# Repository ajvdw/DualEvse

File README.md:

# DualEvse
 Dual EVSE board (Arduino Nano Shield)

Supports charging of 2 vehicles by load balancing between them.
DualEVSE firmware is under development.

You can use OpenEVSE firmware with minor changes if you only need a single charge port.

Please note: The current hardware version (0.9) is not tested yet.

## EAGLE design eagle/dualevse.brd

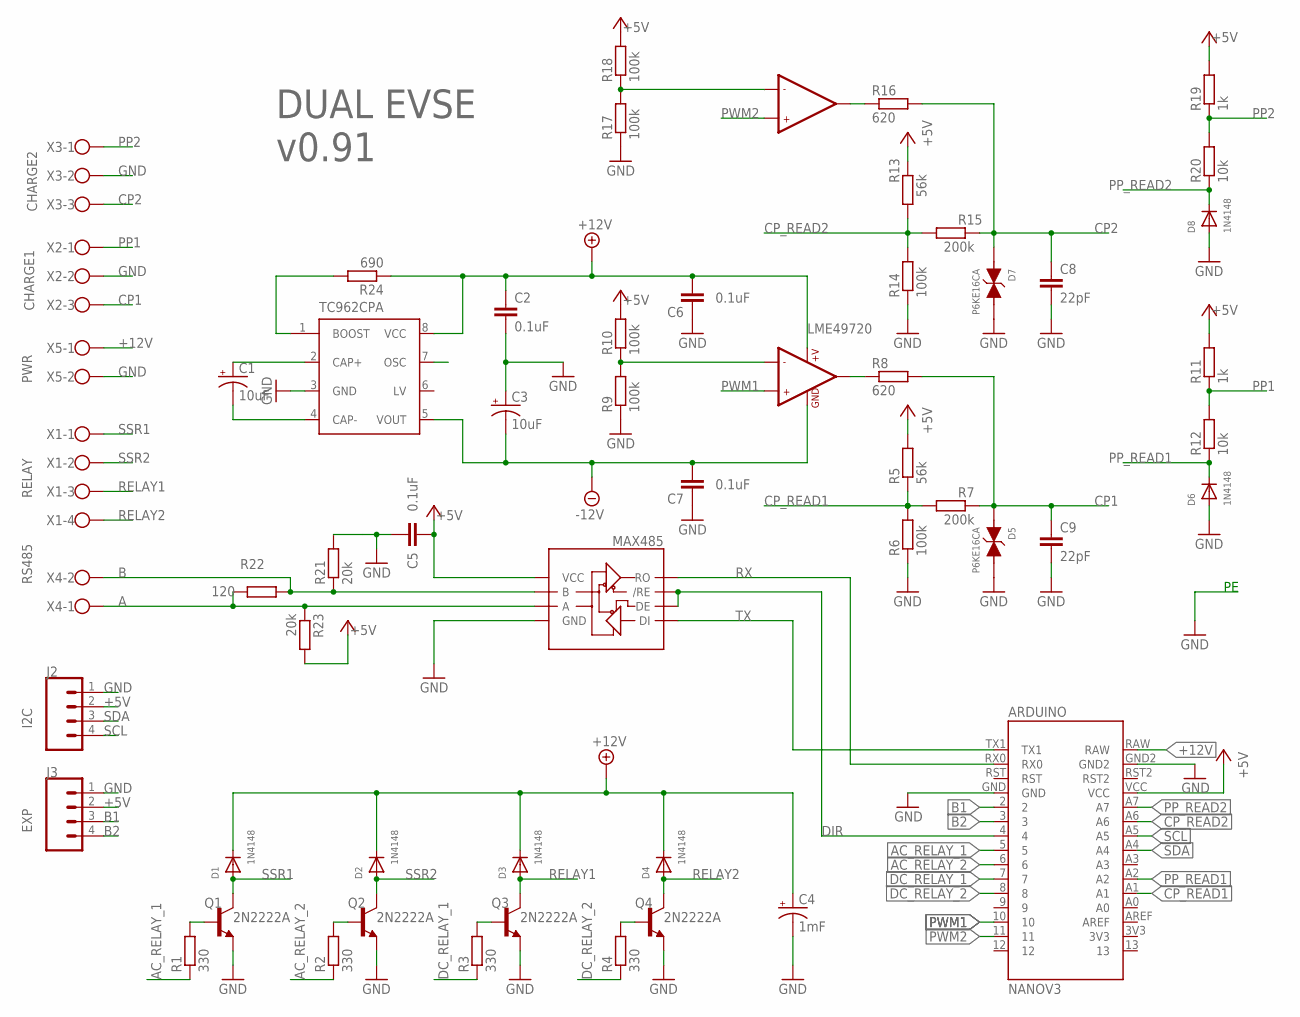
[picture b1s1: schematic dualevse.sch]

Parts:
ARDUINO: NANOV3
C1, C3: 10uF; CPOL-RADIAL-2.5MM-5MM
C2, C5, C6, C7: 0.1uF; CAP-PTH-SMALL-KIT
C4: 1mF; CPOL-RADIAL-5MM-10MM
C8, C9: 22pF; CAP-PTH-2.54
D1, D2, D3, D4, D6, D8: 1N4148; DO-1N4148
D5, D7: P6KE16CA; C4111-15
J2: I2C; MOLEX-1X4
J3: EXP; MOLEX-1X4
LME49720: LME49720; TEXAS_DIL08
MAX485: SPARKFUN-IC-COMMS_RS485; TEXAS_DIL08
Q1, Q2, Q3, Q4: 2N2222A; TO18
R1, R2, R3, R4: 330; 0207/10
R5, R13: 56k; 0207/10
R6, R9, R10, R14, R17, R18: 100k; 0207/10
R7, R15: 200k; 0207/10
R8, R16: 620; 0207/10
R11, R19: 1k; 0207/10
R12, R20: 10k; 0207/10
R21, R23: 20k; 0207/10
R22: 120; 0207/10
R24: 690; 0207/10
TC962CPA: TEXAS_TL7660; TEXAS_DIL08
X1: RELAY; W237-4
X2: CHARGE1; W237-103
X3: CHARGE2; W237-103
X4: RS485; W237-102
X5: PWR; W237-102

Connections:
+5V: ARDUINO.VCC, C5.2, J2.2, J3.2, MAX485.8 (VCC), R5.2, R10.2, R11.2, R13.2, R18.2, R19.2, R23.2
+12V: ARDUINO.RAW, C2.1, C4.+, C6.1, D1.C, D2.C, D3.C, D4.C, LME49720.8 (+V), R24.1, TC962CPA.8 (VCC), X5.1
-12V: C3.2 (-), C7.2, LME49720.4 (GND), TC962CPA.5 (VOUT)
A: MAX485.6 (A), R22.1, R23.1, X4.1
AC_RELAY_1: ARDUINO.5, R1.1
AC_RELAY_2: ARDUINO.6, R2.1
B: MAX485.7 (B), R21.1, R22.2, X4.2
B1: ARDUINO.2, J3.3
B2: ARDUINO.3, J3.4
CP1: C9.1, D5.A (1), R7.2, R8.2, X2.3
CP2: C8.1, D7.A (1), R15.2, R16.2, X3.3
CP_READ1: ARDUINO.A1, R5.1, R6.2, R7.1
CP_READ2: ARDUINO.A6, R13.1, R14.2, R15.1
DC_RELAY_1: ARDUINO.7, R3.1
DC_RELAY_2: ARDUINO.8, R4.1
DIR: ARDUINO.4, MAX485.2 (/RE), MAX485.3 (DE)
GND: ARDUINO.GND, ARDUINO.GND2, C2.2, C3.1 (+), C4.-, C5.1, C6.2, C7.1, C8.2, C9.2, D5.C (2), D6.A, D7.C (2), D8.A, J2.1, J3.1, MAX485.5 (GND), Q1.1 (E), Q2.1 (E), Q3.1 (E), Q4.1 (E), R6.1, R9.1, R14.1, R17.1, R21.2, TC962CPA.3 (GND), X2.2, X3.2, X5.2
unnamed: LME49720.6 (-IN2), R17.2, R18.1
unnamed: Q3.2 (B), R3.2
unnamed: Q4.2 (B), R4.2
unnamed: LME49720.7 (OUT2), R16.1
unnamed: Q1.2 (B), R1.2
unnamed: Q2.2 (B), R2.2
unnamed: R24.2, TC962CPA.1 (BOOST)
unnamed: LME49720.2 (-IN1), R9.2, R10.1
unnamed: LME49720.1 (OUT1), R8.1
unnamed: C1.1 (+), TC962CPA.2 (CAP+)
unnamed: C1.2 (-), TC962CPA.4 (CAP-)
NC: TC962CPA.7 (OSC)
PP1: R11.1, R12.2, X2.1
PP2: R19.1, R20.2, X3.1
PP_READ1: ARDUINO.A2, D6.C, R12.1
PP_READ2: ARDUINO.A7, D8.C, R20.1
PWM1: ARDUINO.10, LME49720.3 (+IN1)
PWM2: ARDUINO.11, LME49720.5 (+IN2)
RELAY1: D3.A, Q3.3 (C), X1.3
RELAY2: D4.A, Q4.3 (C), X1.4
RX: ARDUINO.RX0, MAX485.1 (RO)
SCL: ARDUINO.A5, J2.4
SDA: ARDUINO.A4, J2.3
SSR1: D1.A, Q1.3 (C), X1.1
SSR2: D2.A, Q2.3 (C), X1.2
TX: ARDUINO.TX1, MAX485.4 (DI)

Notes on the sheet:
DUAL EVSE v0.91

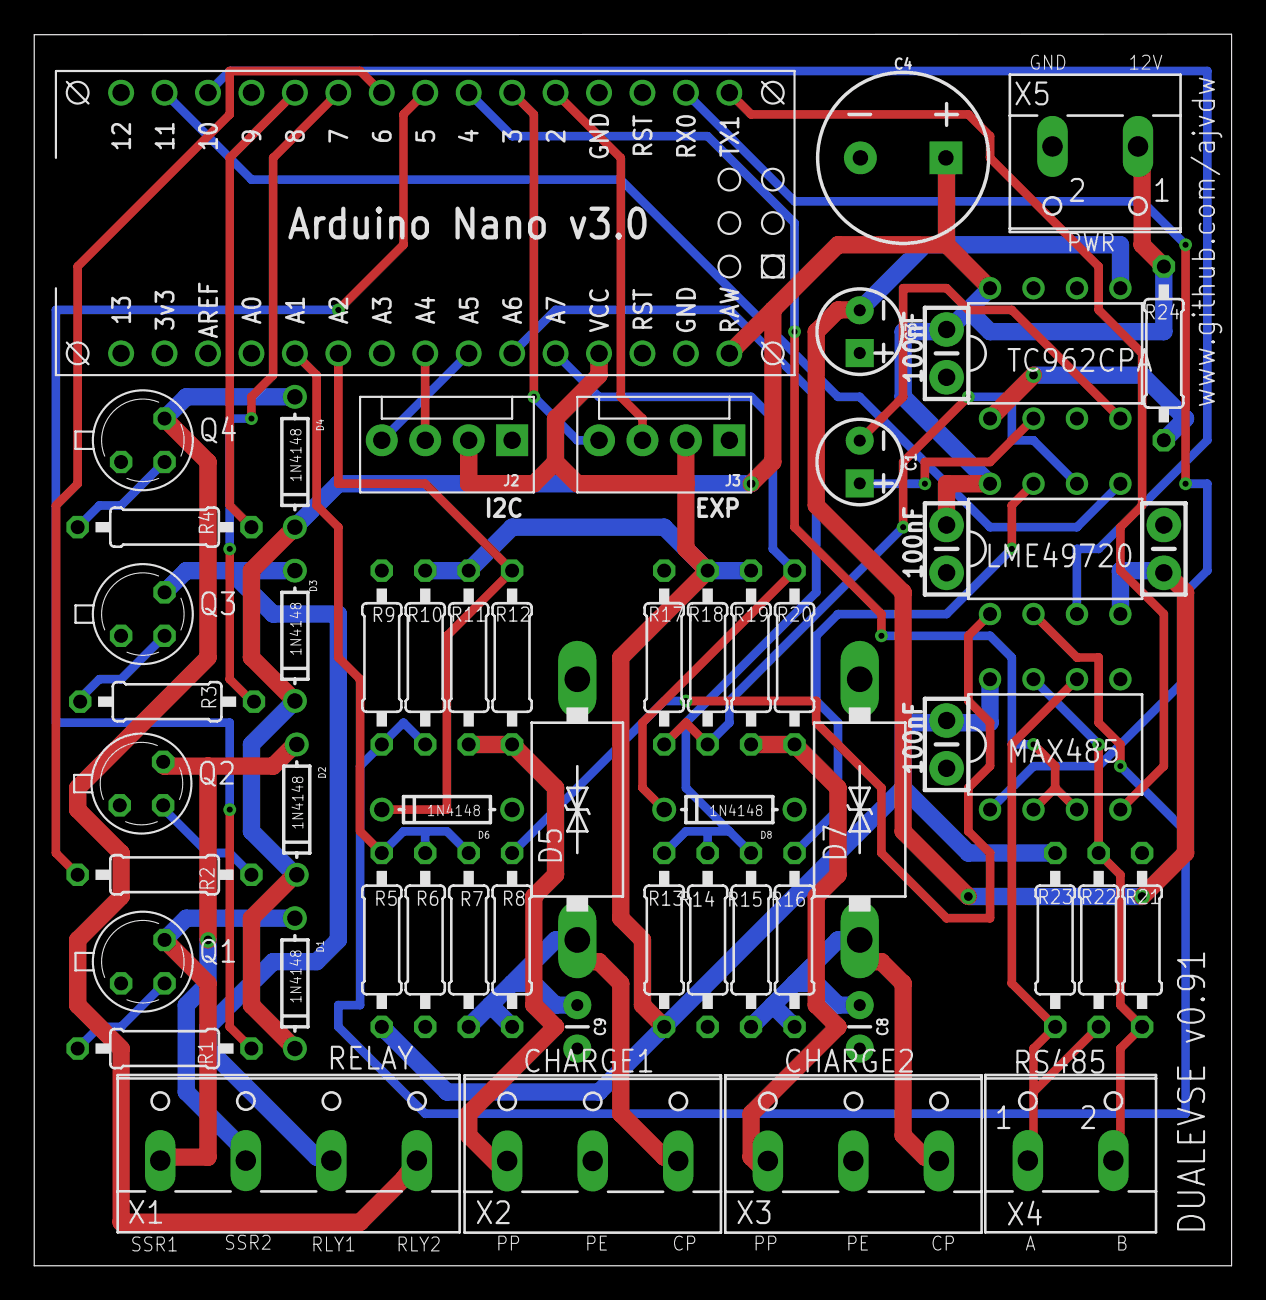
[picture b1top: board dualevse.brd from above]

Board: 2 copper layers, 70.0 x 72.0 mm, 56 parts (0 on the bottom side), 42 nets.

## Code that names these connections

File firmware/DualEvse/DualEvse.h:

/*
Project: DualEVSE
Date:    September 2019

Copyright (c) 2019- AJ vd Werken

Permission is hereby granted, free of charge, to any person obtaining a copy
of this software and associated documentation files (the "Software"), to deal
in the Software without restriction, including without limitation the rights
to use, copy, modify, merge, publish, distribute, sublicense, and/or sell
copies of the Software, and to permit persons to whom the Software is
furnished to do so, subject to the following conditions:

The above copyright notice and this permission notice shall be included in all
copies or substantial portions of the Software.

THE SOFTWARE IS PROVIDED "AS IS", WITHOUT WARRANTY OF ANY KIND, EXPRESS OR
IMPLIED, INCLUDING BUT NOT LIMITED TO THE WARRANTIES OF MERCHANTABILITY,
FITNESS FOR A PARTICULAR PURPOSE AND NONINFRINGEMENT. IN NO EVENT SHALL THE
AUTHORS OR COPYRIGHT HOLDERS BE LIABLE FOR ANY CLAIM, DAMAGES OR OTHER
LIABILITY, WHETHER IN AN ACTION OF CONTRACT, TORT OR OTHERWISE, ARISING FROM,
OUT OF OR IN CONNECTION WITH THE SOFTWARE OR THE USE OR OTHER DEALINGS IN THE
SOFTWARE.
*/
#ifndef DUALEVSE_H
#define DUALEVSE_H

// Not Set, Not Connected, Connected Not Ready, Connected Ready, Connected Requires Ventilation
enum STATE { ST__, ST_A, ST_B, ST_C, ST_D }; 

// Possible CP values
enum PILOT { CP_ERROR, CP_12V, CP_9V, CP_6V, CP_DIODE };

// Hardware PIN layout - Arduino NANO
#define PIN_CP_READ1 1
#define PIN_CP_READ2 2
#define PIN_PP_READ1 3
#define PIN_PP_READ2 4
#define PIN_PWM1     5  
#define PIN_PWM2     6
#define PIN_EXT1     7
#define PIN_EXT2     8
#define PIN_SSR1     9
#define PIN_SSR2    10
#define PIN_RELAY1  11
#define PIN_RELAY2  12

// Configuration values
struct strConfig{
  byte MinCurrentEV[2];
  byte MaxCurrentEV[2];
  byte Contacter[2];
  byte Solenoid[2];
  byte CableLocked[2]; //EVSE2 is always fixed
};

#endif

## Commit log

2019-10-06 Cleanupu
2019-10-06 Changed some texts
2019-10-06 cam generated
2019-10-06 Added version number
2019-10-06 Placeholder for Firmware
2019-10-06 Code change read write config
2019-10-12 Base version
    Pin numbers are not set properly.
2019-10-13 version 0.91
    added 2 capacitors
2019-10-13 v 0.91a

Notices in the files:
parts and their libraries:
SparkFun-Connectors: Licensing: Creative Commons ShareAlike 4.0 International - https://creativecommons.org/licenses/by-sa/4.0
